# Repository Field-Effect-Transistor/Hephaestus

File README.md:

***

# Hephaestus: Smart Soldering Station (T12 + 858D)

**Бакалаврська кваліфікаційна робота**  
Розробка мікрокомп'ютерної системи керування двоканальною паяльною станцією з прецизійним терморегулюванням та апаратною відмовобезпекою.

## 📋 Основні можливості
*   **Два незалежні канали:** Контактний паяльник (жало T12) та компресорний термофен (858D).
*   **Прецизійна точність:** ПІД-регулювання з використанням зовнішнього 16-бітного АЦП та підсилювачів Zero-Drift.
*   **Апаратна безпека:** Електромеханічне реле із системою "самопідхвату" для захисту від термічного пробою.
*   **Багатозадачність (RTOS):** Використання FreeRTOS із витискальною багатозадачністю для суворого дотримання таймінгів алгоритму часового розділення (Time-Division).
*   **HIL Simulation:** Архітектура коду (Dependency Inversion) дозволяє компілювати та тестувати бізнес-логіку станції як нативну Linux/PC програму (Симулятор).
*   **Інтерфейс:** 1.3" OLED дисплей (u8g2) та апаратне декодування квадратурних енкодерів.

## 🛠 Технічний стек

### Апаратна частина (Hardware)
*   **MCU:** STM32F103C8T6 (ARM Cortex-M3)
*   **ADC:** ADS1115 (16-bit, I2C, ΔΣ)
*   **OpAmp:** OPA2333 / MCP6002
*   **Power:** Багаторівнева система живлення (24V, 5V, 3.3V Digital, 3.3V Analog)
*   **Drivers:** MOSFET (T12 / Турбіна), Triac BTA16 + Optocoupler (Нагрівач 220В)
*   **EDA:** KiCad 8.0

### Програмна частина (Firmware)
*   **Language:** C++17 / C
*   **Framework:** STM32 HAL / LL
*   **OS:** FreeRTOS (ARM CM3 Port / POSIX Port для симулятора)
*   **Build System:** CMake + Ninja
*   **IDE:** Visual Studio Code (C/C++ Extension Pack)

## 📂 Структура репозиторію

```text
├── firmware/
│   ├── App/             # Бізнес-логіка, Інтерфейси (C++)
│   │   ├── interfaces/  # Апаратні абстракції (Hardware Agnostic)
│   │   ├── logic/       # ПІД-регулятор, автомати станів кнопок
│   │   ├── platform/    # Реалізація інтерфейсів (STM32 HAL або PC Mocks)
│   │   └── ui/          # Керування дисплеєм (u8g2)
│   ├── Core/            # Згенерований CubeMX код (main.c, freertos.c)
│   ├── Drivers/         # STM32 HAL & CMSIS
│   └── Libs/            # Сторонні бібліотеки (u8g2, FreeRTOS POSIX)
│
├── hardware/            # Схемотехніка та плати (KiCad)
└── docs/                # Пояснювальна записка та даташити
```

## 🚀 Як зібрати проєкт

Проєкт підтримує дві цілі збірки: **Прошивка для мікроконтролера (STM32)** та **Симулятор для комп'ютера (Linux/PC)**.

### 1. Збірка Симулятора (Linux)
Симулятор компілює всю бізнес-логіку, запускає FreeRTOS поверх Pthreads операційної системи Linux та імітує датчики за допомогою об'єктів-заглушок (Mocks). Це дозволяє тестувати систему без реальної плати.

**Вимоги:** `cmake`, `ninja`, `gcc`, `g++`.

```bash
cd firmware
mkdir -p build_pc
rm -rf build_pc/* 

# Генеруємо конфігурацію для симулятора
cmake -DBUILD_SIMULATOR=ON -DCMAKE_C_COMPILER=gcc -DCMAKE_CXX_COMPILER=g++ . -G Ninja -B build_pc   

# Збираємо проєкт
ninja -C build_pc 

# Запускаємо симулятор
./build_pc/Hephaestus_Sim
```

### 2. Збірка Прошивки (STM32)
Для крос-компіляції під мікроконтролер використовується офіційний Toolchain.

**Вимоги:** `arm-none-eabi-gcc`, `cmake`, `ninja`.

```bash
cd firmware
mkdir -p build
rm -rf build/*

# Генеруємо конфігурацію для крос-компіляції
cmake -DCMAKE_TOOLCHAIN_FILE=cmake/gcc-arm-none-eabi.cmake . -G Ninja -B build

# Збираємо прошивку (.elf, .bin, .hex)
ninja -C build
```

***

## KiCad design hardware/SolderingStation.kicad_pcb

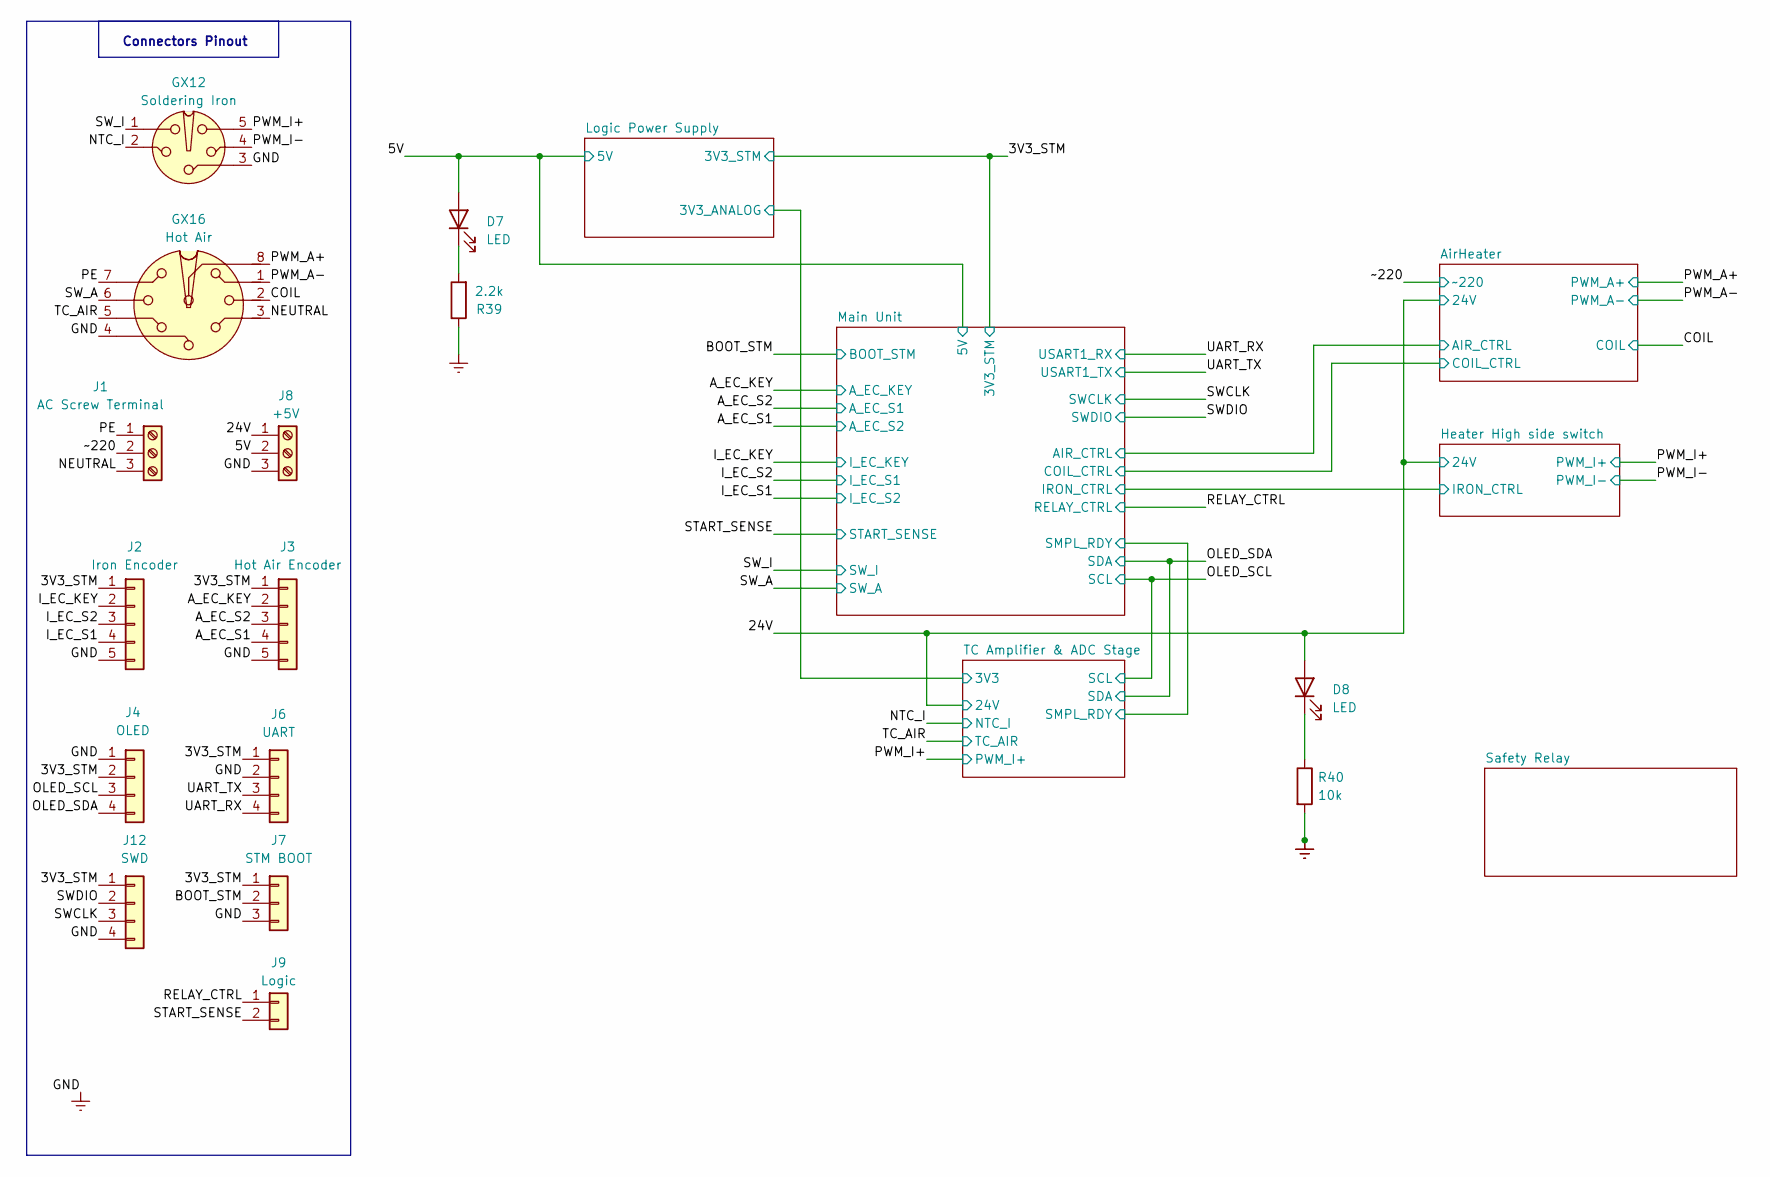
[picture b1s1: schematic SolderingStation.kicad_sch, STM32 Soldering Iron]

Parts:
D7, D8: LED; LED_0805_2012Metric_Pad1.15x1.40mm_HandSolder; LCSC C2286
GX12: Soldering Iron; GX-12-5
GX16: Hot Air; GX-16-8
J1: AC Screw Terminal; TerminalBlock_MaiXu_MX126-5.0-03P_1x03_P5.00mm
J2: Iron Encoder; PinHeader_1x05_P2.54mm_Vertical
J3: Hot Air Encoder; PinHeader_1x05_P2.54mm_Vertical
J4: OLED; PinHeader_1x04_P2.54mm_Vertical
J6: UART; PinHeader_1x04_P2.54mm_Vertical
J7: STM BOOT; PinHeader_1x03_P2.54mm_Vertical
J8: +5V; TerminalBlock_MaiXu_MX126-5.0-03P_1x03_P5.00mm
J9: Logic; PinHeader_1x02_P2.54mm_Vertical
J12: SWD; PinHeader_1x04_P2.54mm_Vertical
R39: 2.2k; R_0805_2012Metric_Pad1.20x1.40mm_HandSolder; LCSC C4190
R40: 10k; R_0805_2012Metric_Pad1.20x1.40mm_HandSolder; LCSC C25804

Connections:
/3V3_STM: J2.1, J3.1, J4.2, J6.1, J7.1, J12.1; also elsewhere on the board
/5V: D7.2 (A), J8.2; also elsewhere on the board
/24V: D8.2 (A), GX16.8, J8.1; also elsewhere on the board
/A_EC_KEY: J3.2; also elsewhere on the board
/A_EC_S1: J3.4; also elsewhere on the board
/A_EC_S2: J3.3; also elsewhere on the board
/BOOT_STM: J7.2; also elsewhere on the board
/COIL: GX16.2; also elsewhere on the board
/I_EC_KEY: J2.2; also elsewhere on the board
/I_EC_S1: J2.4; also elsewhere on the board
/I_EC_S2: J2.3; also elsewhere on the board
/NEUTRAL: GX16.3, J1.3
/NTC_I: GX12.2; also elsewhere on the board
/OLED_SCL: J4.3; also elsewhere on the board
/OLED_SDA: J4.4; also elsewhere on the board
/PE: GX16.7, J1.1
/PWM_A-: GX16.1; also elsewhere on the board
/PWM_I+: GX12.5; also elsewhere on the board
/RELAY_CTRL: J9.1; also elsewhere on the board
/START_SENSE: J9.2; also elsewhere on the board
/SWCLK: J12.3; also elsewhere on the board
/SWDIO: J12.2; also elsewhere on the board
/SW_A: GX16.6; also elsewhere on the board
/SW_I: GX12.1; also elsewhere on the board
/TC_AIR: GX16.5; also elsewhere on the board
/UART_RX: J6.4; also elsewhere on the board
/UART_TX: J6.3; also elsewhere on the board
/~220: J1.2; also elsewhere on the board
GNDREF: GX12.3, GX12.4, GX16.4, J2.5, J3.5, J4.1, J6.2, J7.3, J8.3, J12.4, R39.1, R40.2; also elsewhere on the board
unnamed: D7.1 (K), R39.2
unnamed: D8.1 (K), R40.1

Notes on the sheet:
Connectors Pinout

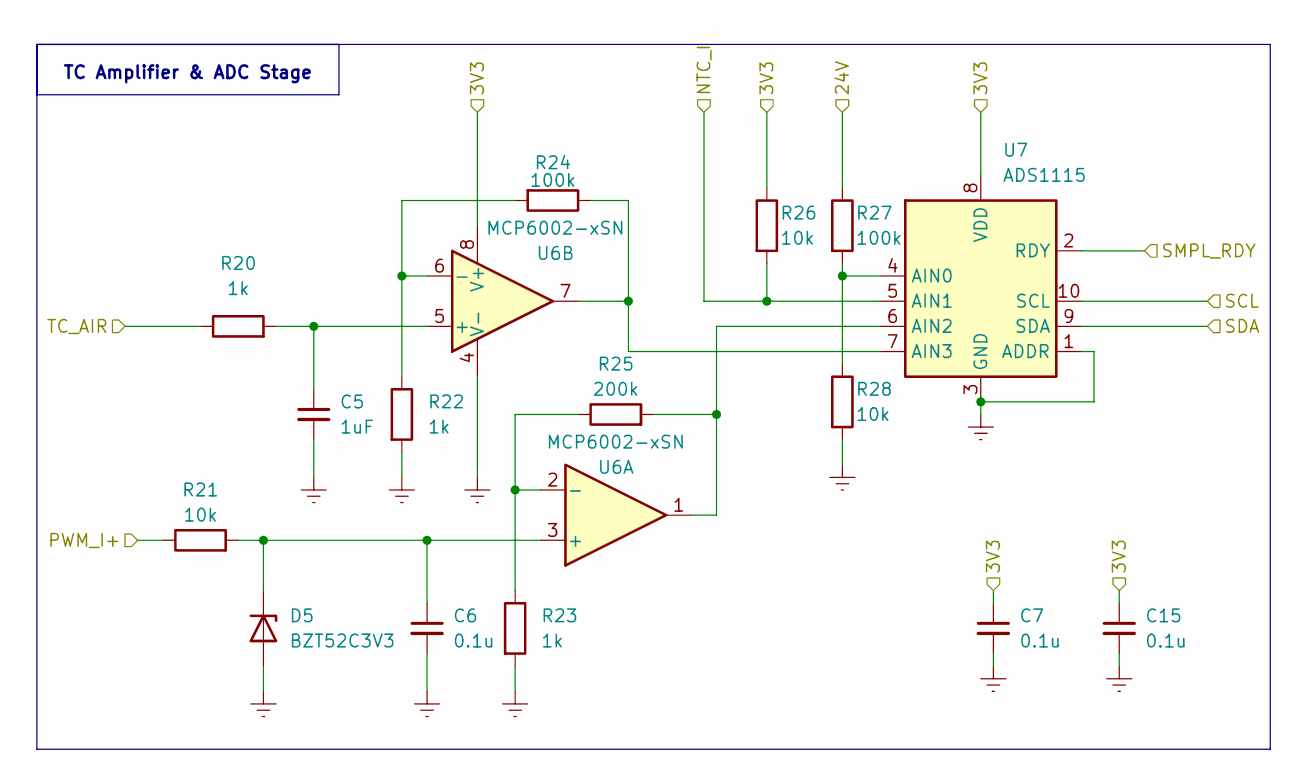
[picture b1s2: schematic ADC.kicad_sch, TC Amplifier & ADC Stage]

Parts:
C5: 1uF; C_0805_2012Metric_Pad1.18x1.45mm_HandSolder; LCSC C1634
C6, C7, C15: 0.1u; C_0805_2012Metric_Pad1.18x1.45mm_HandSolder; LCSC C14663
D5: BZT52C3V3; D_DO-35_SOD27_P2.54mm_Vertical_AnodeUp
R20, R22, R23: 1k; R_0805_2012Metric_Pad1.20x1.40mm_HandSolder; LCSC C21190
R21, R26, R28: 10k; R_0805_2012Metric_Pad1.20x1.40mm_HandSolder; LCSC C25804
R24, R27: 100k; R_0805_2012Metric_Pad1.20x1.40mm_HandSolder; LCSC C25803
R25: 200k; R_0805_2012Metric_Pad1.20x1.40mm_HandSolder; LCSC C25811
U6: MCP6002-xSN; SOIC-8_3.9x4.9mm_P1.27mm
U7: ADS1115; MSOP-10_3x3mm_P0.5mm

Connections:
/24V: R27.1; also elsewhere on the board
/Logic Power Supply/3V3_ANALOG: C7.1, C15.1, R26.1, U6.8 (V+), U7.8 (VDD); also elsewhere on the board
/Main Unit/SMPL_RDY: U7.2 (RDY); also elsewhere on the board
/NTC_I: R26.2, U7.5 (AIN1); also elsewhere on the board
/OLED_SCL: U7.10 (SCL); also elsewhere on the board
/OLED_SDA: U7.9 (SDA); also elsewhere on the board
/PWM_I+: R21.1; also elsewhere on the board
/TC_AIR: R20.1; also elsewhere on the board
GNDREF: C5.2, C6.2, C7.2, C15.2, D5.2 (A), R22.2, R23.2, R28.2, U6.4 (V-), U7.1 (ADDR), U7.3 (GND); also elsewhere on the board
unnamed: C6.1, D5.1 (K), R21.2, U6.3 (+)
unnamed: R23.1, R25.1, U6.2 (-)
unnamed: C5.1, R20.2, U6.5 (+)
unnamed: R22.1, R24.2, U6.6 (-)
unnamed: R27.2, R28.1, U7.4 (AIN0)
unnamed: R25.2, U6.1, U7.6 (AIN2)
unnamed: R24.1, U6.7, U7.7 (AIN3)

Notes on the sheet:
TC Amplifier & ADC Stage

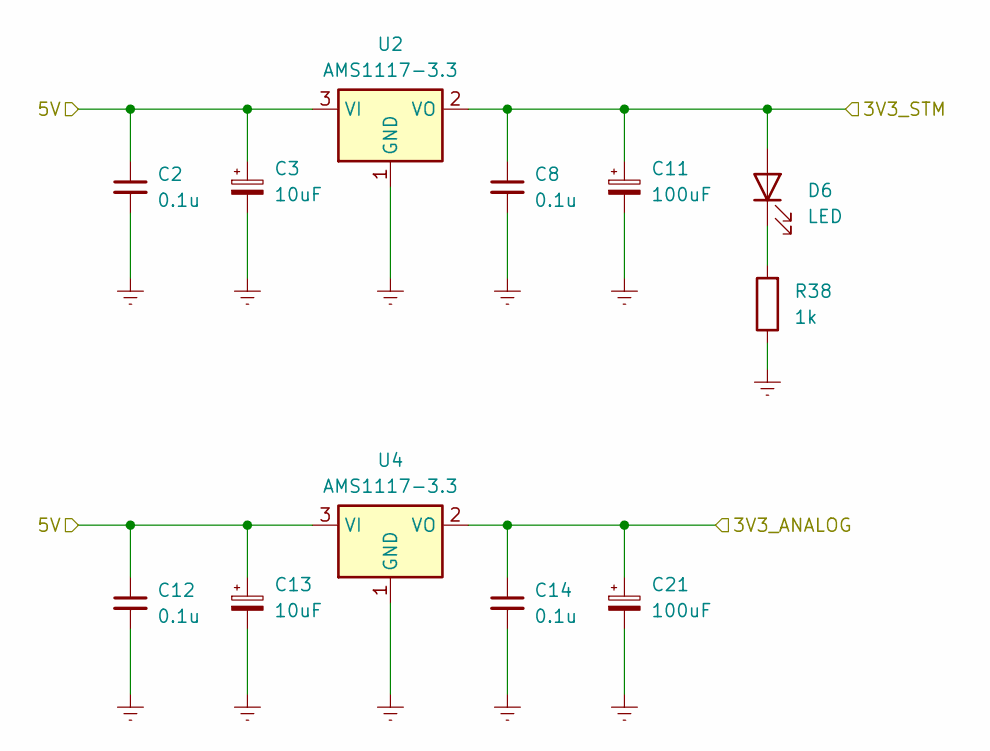
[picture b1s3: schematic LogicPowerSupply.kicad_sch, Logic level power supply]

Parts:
C2, C8, C12, C14: 0.1u; C_0805_2012Metric_Pad1.18x1.45mm_HandSolder; LCSC C14663
C3, C13: 10uF; CP_Radial_D5.0mm_P2.00mm
C11, C21: 100uF; CP_Radial_D6.3mm_P2.50mm
D6: LED; LED_0805_2012Metric_Pad1.15x1.40mm_HandSolder; LCSC C2286
R38: 1k; R_0805_2012Metric_Pad1.20x1.40mm_HandSolder; LCSC C21190
U2, U4: AMS1117-3.3; SOT-223-3_TabPin2; LCSC C6186

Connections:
/3V3_STM: C8.1, C11.1, D6.2 (A), U2.2 (VO); also elsewhere on the board
/5V: C2.1, C3.1, C12.1, C13.1, U2.3 (VI), U4.3 (VI); also elsewhere on the board
/Logic Power Supply/3V3_ANALOG: C14.1, C21.1, U4.2 (VO); also elsewhere on the board
GNDREF: C2.2, C3.2, C8.2, C11.2, C12.2, C13.2, C14.2, C21.2, R38.1, U2.1 (GND), U4.1 (GND); also elsewhere on the board
unnamed: D6.1 (K), R38.2

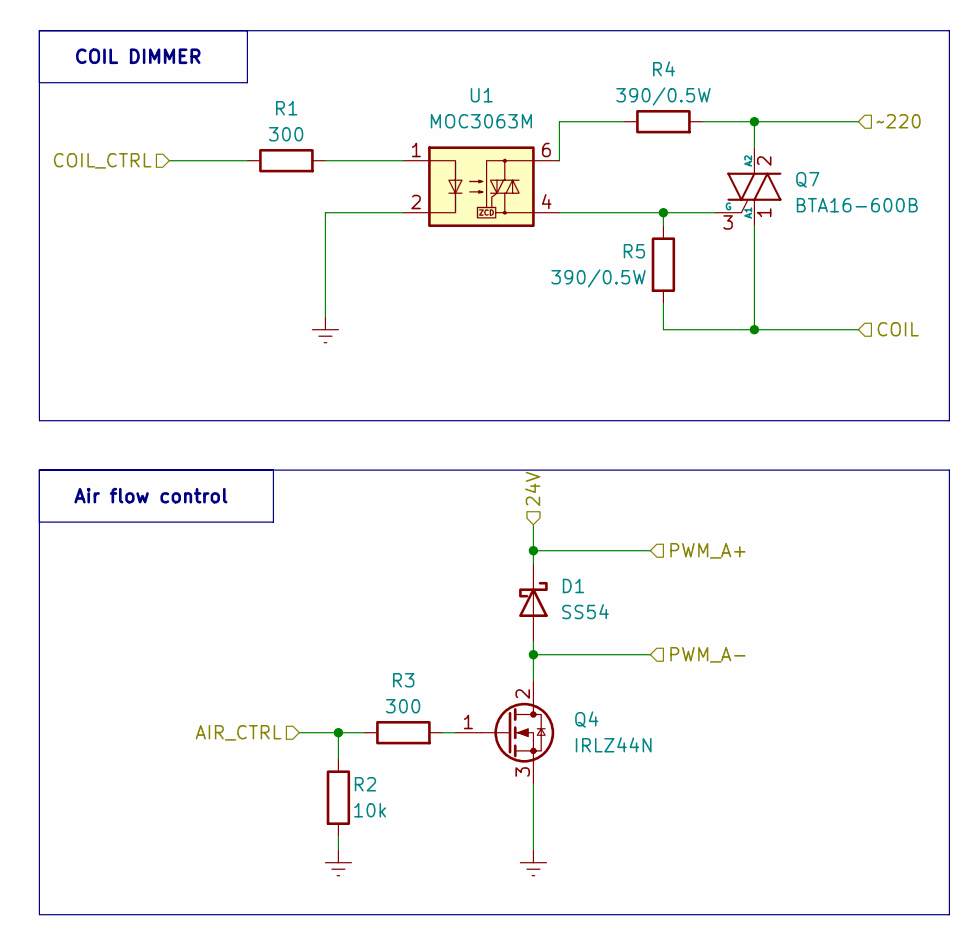
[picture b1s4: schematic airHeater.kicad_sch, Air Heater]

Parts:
D1: SS54; D_SMA; LCSC C22452
Q4: IRLZ44N; TO-220-3_Vertical
Q7: BTA16-600B; TO-220-3_Vertical
R1, R3: 300; R_0805_2012Metric_Pad1.20x1.40mm_HandSolder; LCSC C23025
R2: 10k; R_0805_2012Metric_Pad1.20x1.40mm_HandSolder; LCSC C25804
R4, R5: 390/0.5W; R_Axial_DIN0309_L9.0mm_D3.2mm_P12.70mm_Horizontal
U1: MOC3063M; DIP-6_W7.62mm_LongPads

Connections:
/24V: D1.1 (K); also elsewhere on the board
/AirHeater/AIR_CTRL: R2.1, R3.1; also elsewhere on the board
/AirHeater/COIL_CTRL: R1.1; also elsewhere on the board
/COIL: Q7.1 (A1), R5.2; also elsewhere on the board
/PWM_A-: D1.2 (A), Q4.2 (D); also elsewhere on the board
/~220: Q7.2 (A2), R4.2; also elsewhere on the board
GNDREF: Q4.3 (S), R2.2, U1.2; also elsewhere on the board
unnamed: Q4.1 (G), R3.2
unnamed: Q7.3 (G), R5.1, U1.4
unnamed: R1.2, U1.1
unnamed: R4.1, U1.6

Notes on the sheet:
COIL DIMMER
Air flow control

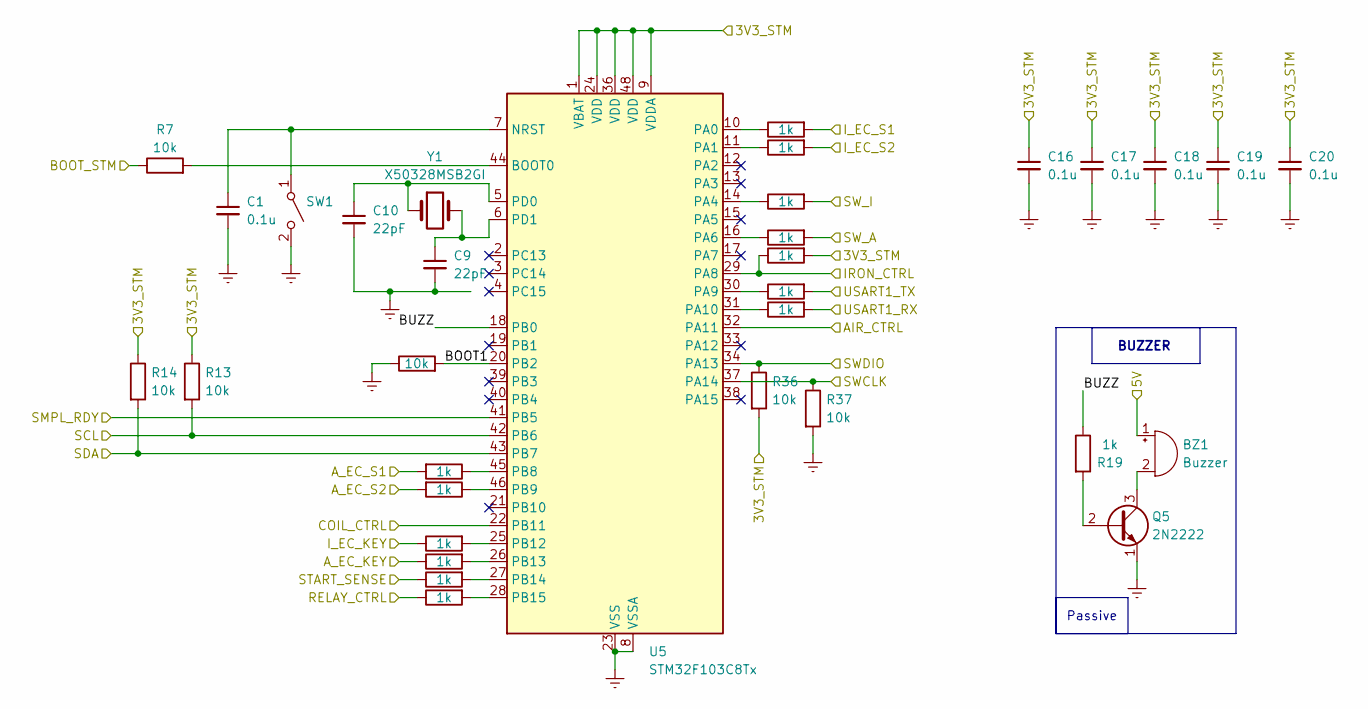
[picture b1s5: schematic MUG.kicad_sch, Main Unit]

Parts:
BZ1: Buzzer; Buzzer_12x9.5RM7.6
C1, C16, C17, C18, C19, C20: 0.1u; C_0805_2012Metric_Pad1.18x1.45mm_HandSolder; LCSC C14663
C9, C10: 22pF; C_0805_2012Metric_Pad1.18x1.45mm_HandSolder; LCSC C1653
Q5: 2N2222; TO-92_Inline; LCSC C2146
R6, R7, R13, R14, R36, R37: 10k; R_0805_2012Metric_Pad1.20x1.40mm_HandSolder; LCSC C25804
R12, R15, R17, R18, R19, R29, R30, R31, R32, R33, R34, R35, R41, R42: 1k; R_0805_2012Metric_Pad1.20x1.40mm_HandSolder; LCSC C21190
SW1: SW_SPST; SW_PUSH_6mm_H8mm
U5: STM32F103C8Tx; LQFP-48_7x7mm_P0.5mm
Y1: X50328MSB2GI; Crystal_SMD_5032-2Pin_5.0x3.2mm; LCSC C115962

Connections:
/3V3_STM: C16.1, C17.1, C18.1, C19.1, C20.1, R13.1, R14.1, R15.2, R36.2, U5.1 (VBAT), U5.9 (VDDA), U5.24 (VDD), U5.36 (VDD), U5.48 (VDD); also elsewhere on the board
/5V: BZ1.1 (+); also elsewhere on the board
/A_EC_KEY: R30.1; also elsewhere on the board
/A_EC_S1: R32.2; also elsewhere on the board
/A_EC_S2: R31.2; also elsewhere on the board
/AirHeater/AIR_CTRL: U5.32 (PA11); also elsewhere on the board
/AirHeater/COIL_CTRL: U5.22 (PB11); also elsewhere on the board
/BOOT_STM: R7.1; also elsewhere on the board
/Heater High side switch/IRON_CTRL: R15.1, U5.29 (PA8); also elsewhere on the board
/I_EC_KEY: R29.1; also elsewhere on the board
/I_EC_S1: R18.2; also elsewhere on the board
/I_EC_S2: R17.2; also elsewhere on the board
/Main Unit/BOOT1: R6.2, U5.20 (PB2)
/Main Unit/BUZZ: R19.1, U5.18 (PB0)
/Main Unit/SMPL_RDY: U5.41 (PB5); also elsewhere on the board
/OLED_SCL: R13.2, U5.42 (PB6); also elsewhere on the board
/OLED_SDA: R14.2, U5.43 (PB7); also elsewhere on the board
/RELAY_CTRL: R33.1; also elsewhere on the board
/START_SENSE: R12.1; also elsewhere on the board
/SWCLK: R37.1, U5.37 (PA14); also elsewhere on the board
/SWDIO: R36.1, U5.34 (PA13); also elsewhere on the board
/SW_A: R34.2; also elsewhere on the board
/SW_I: R35.2; also elsewhere on the board
/UART_RX: R42.2; also elsewhere on the board
/UART_TX: R41.2; also elsewhere on the board
GNDREF: C1.2, C9.2, C10.2, C16.2, C17.2, C18.2, C19.2, C20.2, Q5.1 (E), R6.1, R37.2, SW1.2 (B), U5.8 (VSSA), U5.23 (VSS), U5.35 (VSS), U5.47 (VSS); also elsewhere on the board
unnamed: BZ1.2 (-), Q5.3 (C)
unnamed: Q5.2 (B), R19.2
unnamed: C1.1, SW1.1 (A), U5.7 (NRST)
unnamed: R7.2, U5.44 (BOOT0)
unnamed: R17.1, U5.10 (PA0)
unnamed: R18.1, U5.11 (PA1)
unnamed: R35.1, U5.14 (PA4)
unnamed: R34.1, U5.16 (PA6)
unnamed: R41.1, U5.30 (PA9)
unnamed: R42.1, U5.31 (PA10)
unnamed: R31.1, U5.45 (PB8)
unnamed: R32.1, U5.46 (PB9)
unnamed: R29.2, U5.25 (PB12)
unnamed: R30.2, U5.26 (PB13)
unnamed: R12.2, U5.27 (PB14)
unnamed: R33.2, U5.28 (PB15)
unnamed: C10.1, U5.5 (PD0), Y1.1
unnamed: C9.1, U5.6 (PD1), Y1.2

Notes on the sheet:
Passive
BUZZER

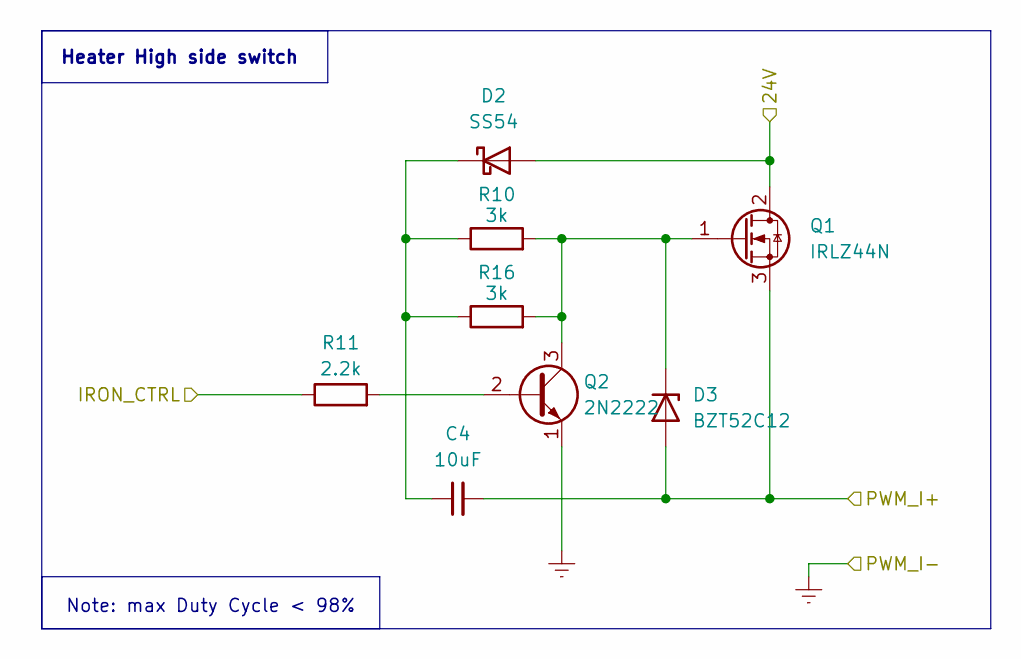
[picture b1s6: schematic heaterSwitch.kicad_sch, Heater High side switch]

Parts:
C4: 10uF; C_1206_3216Metric; LCSC C13585
D2: SS54; D_SMA; LCSC C22452
D3: BZT52C12; D_DO-35_SOD27_P2.54mm_Vertical_AnodeUp
Q1: IRLZ44N; TO-220-3_Vertical
Q2: 2N2222; TO-92_Inline; LCSC C2146
R10, R16: 3k; R_Axial_DIN0207_L6.3mm_D2.5mm_P7.62mm_Horizontal
R11: 2.2k; R_0805_2012Metric_Pad1.20x1.40mm_HandSolder; LCSC C4190

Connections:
/24V: D2.2 (A), Q1.2 (D); also elsewhere on the board
/Heater High side switch/IRON_CTRL: R11.1; also elsewhere on the board
/PWM_I+: C4.2, D3.2 (A), Q1.3 (S); also elsewhere on the board
GNDREF: Q2.1 (E); also elsewhere on the board
unnamed: C4.1, D2.1 (K), R10.1, R16.1
unnamed: D3.1 (K), Q1.1 (G), Q2.3 (C), R10.2, R16.2
unnamed: Q2.2 (B), R11.2

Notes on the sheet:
Note: max Duty Cycle < 98%
Heater High side switch

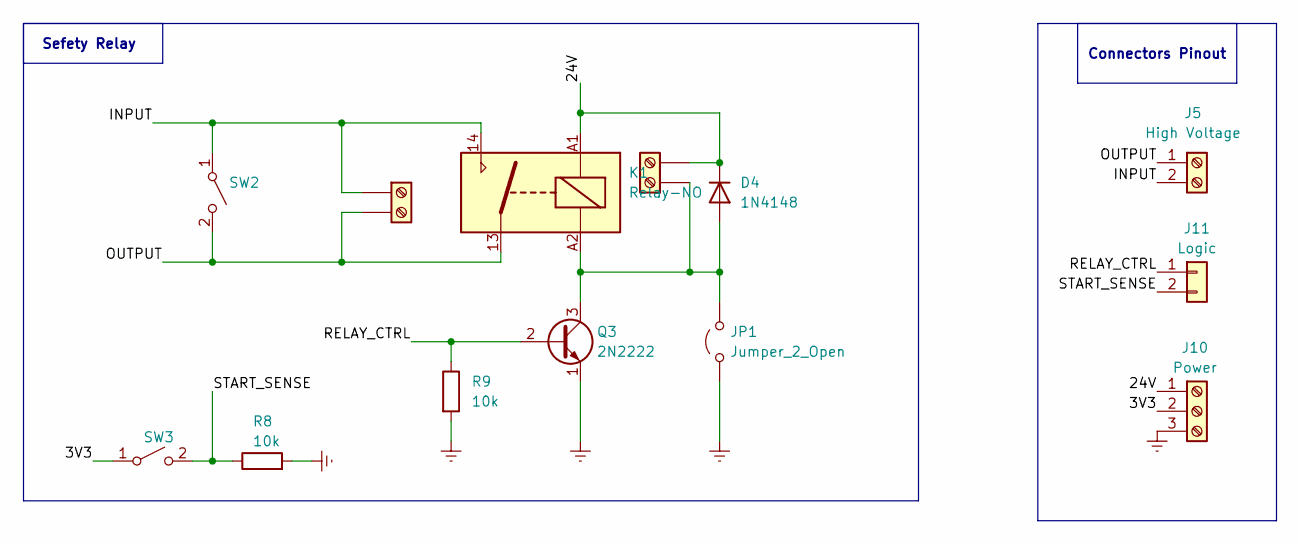
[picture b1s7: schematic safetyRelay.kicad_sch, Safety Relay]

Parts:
D4: 1N4148; D_SOD-123F; LCSC C2128
J5: High Voltage; TerminalBlock_MaiXu_MX126-5.0-02P_1x02_P5.00mm
J10: Power; TerminalBlock_MaiXu_MX126-5.0-03P_1x03_P5.00mm
J11: Logic; PinHeader_1x02_P2.54mm_Vertical
J13: Relay Contact; TerminalBlock_MaiXu_MX126-5.0-02P_1x02_P5.00mm
J14: Relay Coil; TerminalBlock_MaiXu_MX126-5.0-02P_1x02_P5.00mm
JP1: Jumper_2_Open; PinHeader_1x03_P2.54mm_Vertical
K1: Relay-NO; TerminalBlock_MaiXu_MX126-5.0-04P_1x04_P5.00mm
Q3: 2N2222; TO-92_Inline; LCSC C2146
R8, R9: 10k; R_0805_2012Metric_Pad1.20x1.40mm_HandSolder; LCSC C25804
SW2: SW_SPST; TerminalBlock_MaiXu_MX126-5.0-02P_1x02_P5.00mm
SW3: SW_SPST; PinHeader_1x02_P2.54mm_Vertical

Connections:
/Safety Relay/3V3: J10.2, SW3.1 (A)
/Safety Relay/24V: D4.1 (K), J10.1, J14.2, K1.A1
/Safety Relay/INPUT: J5.2, J13.1, K1.14, SW2.1 (A)
/Safety Relay/OUTPUT: J5.1, J13.2, K1.13, SW2.2 (B)
/Safety Relay/RELAY_CTRL: J11.1, Q3.2 (B), R9.1
/Safety Relay/START_SENSE: J11.2, R8.1, SW3.2 (B)
GNDREF: J10.3, JP1.1 (A), Q3.1 (E), R8.2, R9.2; also elsewhere on the board
unnamed: D4.2 (A), J14.1, JP1.2 (B), K1.A2, Q3.3 (C)

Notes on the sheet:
Sefety Relay
Connectors Pinout

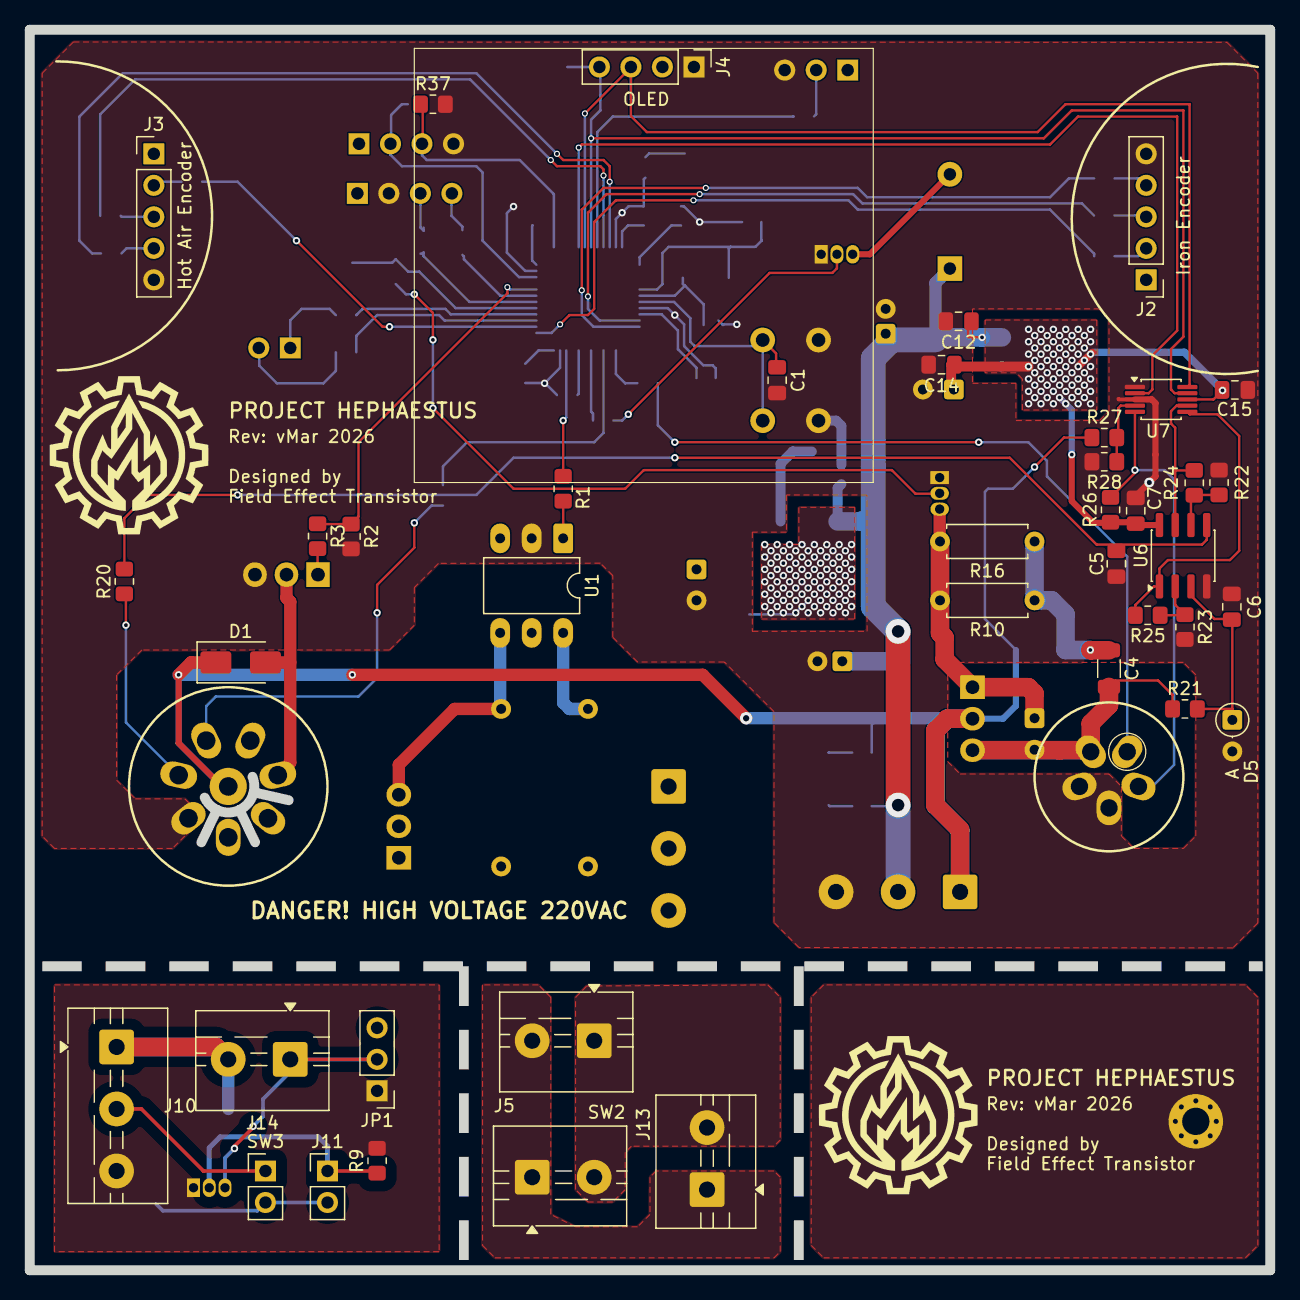
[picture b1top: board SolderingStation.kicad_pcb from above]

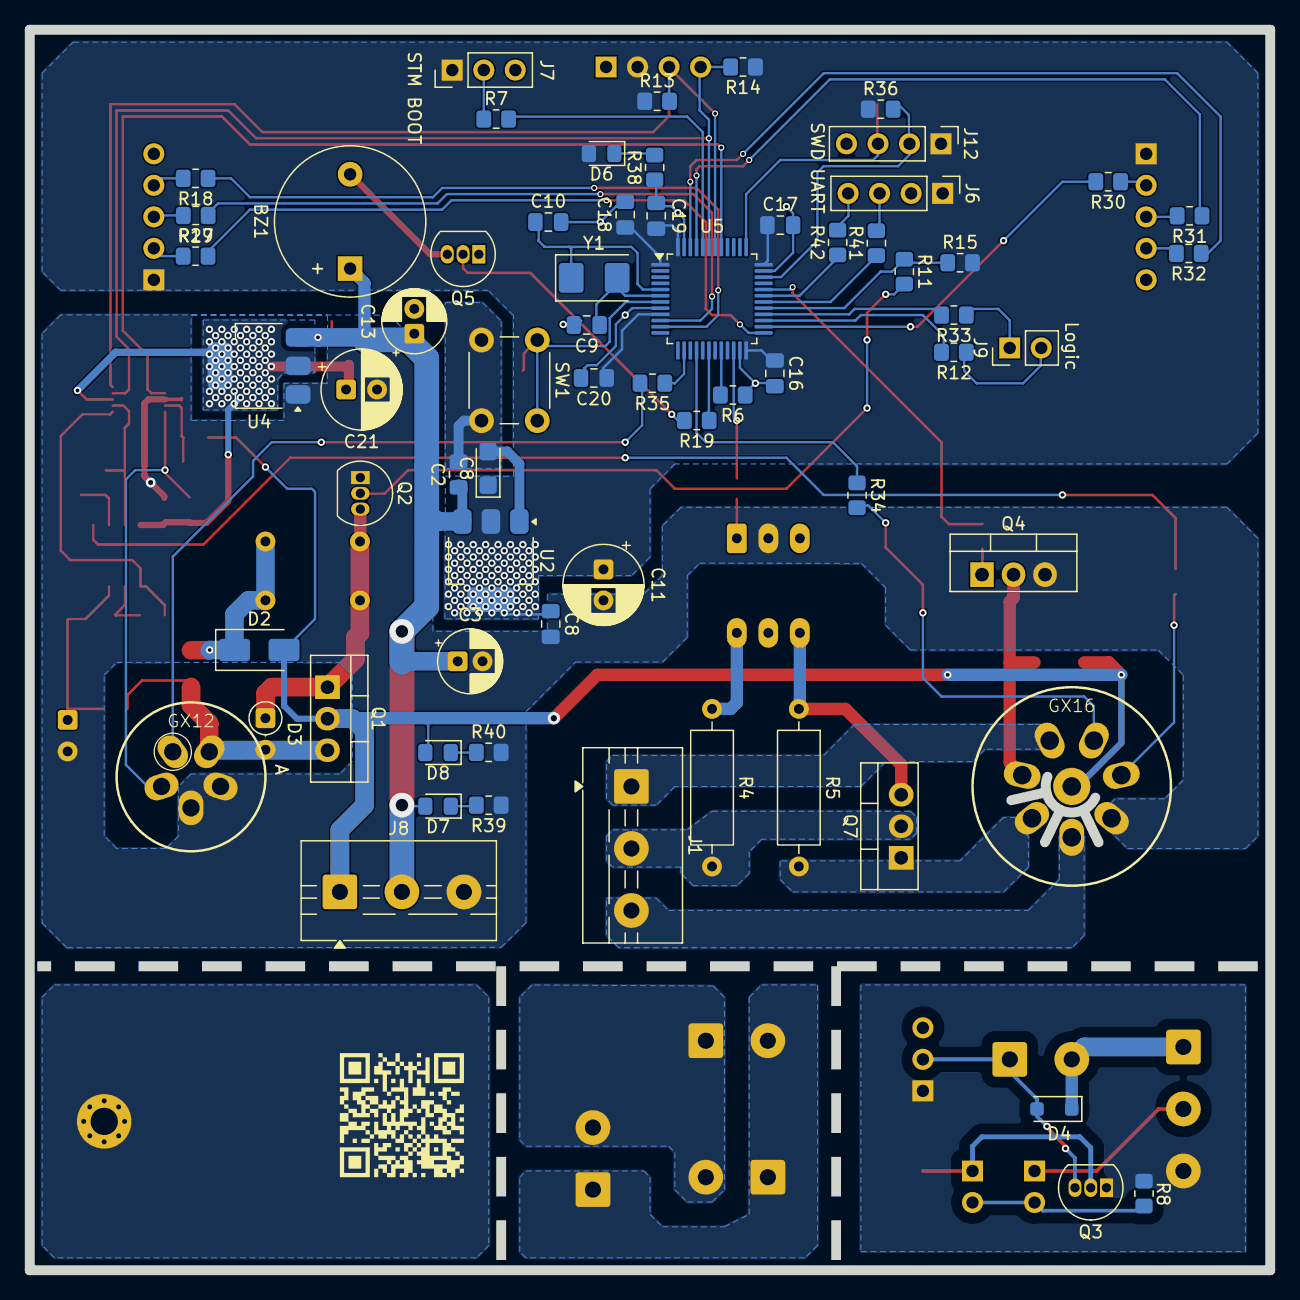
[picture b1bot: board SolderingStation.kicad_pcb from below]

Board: 2 copper layers, 100.0 x 100.0 mm, 106 parts (66 on the bottom side), 78 nets.

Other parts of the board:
C8#2: 0.1u; C_0805_2012Metric_Pad1.18x1.45mm_HandSolder

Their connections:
/3V3_STM: C8#2.1; also elsewhere on the board
GNDREF: C8#2.2; also elsewhere on the board

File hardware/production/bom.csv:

Designator,Footprint,Quantity,Value,LCSC Part #
BZ1,Buzzer_12x9.5RM7.6,1,Buzzer,
"C1, C12, C14, C15, C16, C17, C18, C19, C2, C20, C6, C7, C8",0805,13,0.1u,C14663
"C10, C9",0805,2,22pF,C1653 
"C11, C21",CP_Radial_D6.3mm_P2.50mm,2,100uF,
"C13, C3",CP_Radial_D5.0mm_P2.00mm,2,10uF,
C4,1206,1,10uF,C13585
C5,0805,1,1uF,C1634
C8_2,CP_EIA-3216-18_Kemet-A,1,22uF,
"D1, D2",D_SMA,2,SS54,C22452
D3,D_DO-35_SOD27_P2.54mm_Vertical_AnodeUp,1,BZT52C12,
D4,D_SOD-123F,1,1N4148,C2128
D5,D_DO-35_SOD27_P2.54mm_Vertical_AnodeUp,1,BZT52C3V3,
"D6, D7, D8",0805,3,LED,C2286
GX12,GX-12-5,1,Soldering Iron,
GX16,GX-16-8,1,Hot Air,
J1,TerminalBlock_MaiXu_MX126-5.0-03P_1x03_P5.00mm,1,AC Screw Terminal,
J10,TerminalBlock_MaiXu_MX126-5.0-03P_1x03_P5.00mm,1,Power,
"J11, J9",PinHeader_1x02_P2.54mm_Vertical,2,Logic,
J12,PinHeader_1x04_P2.54mm_Vertical,1,SWD,
J13,TerminalBlock_MaiXu_MX126-5.0-02P_1x02_P5.00mm,1,Relay Contact,
J14,TerminalBlock_MaiXu_MX126-5.0-02P_1x02_P5.00mm,1,Relay Coil,
J2,PinHeader_1x05_P2.54mm_Vertical,1,Iron Encoder,
J3,PinHeader_1x05_P2.54mm_Vertical,1,Hot Air Encoder,
J4,PinHeader_1x04_P2.54mm_Vertical,1,OLED,
J5,TerminalBlock_MaiXu_MX126-5.0-02P_1x02_P5.00mm,1,High Voltage,
J6,PinHeader_1x04_P2.54mm_Vertical,1,UART,
J7,PinHeader_1x03_P2.54mm_Vertical,1,STM BOOT,
J8,TerminalBlock_MaiXu_MX126-5.0-03P_1x03_P5.00mm,1,+5V,
JP1,PinHeader_1x03_P2.54mm_Vertical,1,Jumper_2_Open,
"Q1, Q4",TO-220-3_Vertical,2,IRLZ44N,
"Q2, Q3, Q5",TO-92_Inline,3,2N2222,C2146
Q7,TO-220-3_Vertical,1,BTA16-600B,
"R1, R3",0805,2,300,C23025
"R10, R16",R_Axial_DIN0207_L6.3mm_D2.5mm_P7.62mm_Horizontal,2,3k,
"R11, R39",0805,2,2.2k,C4190
"R12, R15, R17, R18, R19, R20, R22, R23, R29, R30, R31, R32, R33, R34, R35, R38, R41, R42",0805,18,1k,C21190
"R13, R14, R2, R21, R26, R28, R36, R37, R40, R6, R7, R8, R9",0805,13,10k,C25804
"R24, R27",0805,2,100k,C25803
R25,0805,1,200k,C25811
"R4, R5",R_Axial_DIN0309_L9.0mm_D3.2mm_P12.70mm_Horizontal,2,390/0.5W,
SW1,SW_PUSH_6mm_H8mm,1,SW_SPST,
SW2,TerminalBlock_MaiXu_MX126-5.0-02P_1x02_P5.00mm,1,SW_SPST,
SW3,PinHeader_1x02_P2.54mm_Vertical,1,SW_SPST,
U1,DIP-6_W7.62mm_LongPads,1,MOC3063M,
"U2, U4",SOT-223-3_TabPin2,2,AMS1117-3.3,C6186 
U5,LQFP-48_7x7mm_P0.5mm,1,STM32F103C8Tx,
U6,SOIC-8_3.9x4.9mm_P1.27mm,1,MCP6002-xSN,
U7,MSOP-10_3x3mm_P0.5mm,1,ADS1115,
Y1,Crystal_SMD_5032-2Pin_5.0x3.2mm,1,X50328MSB2GI,C115962

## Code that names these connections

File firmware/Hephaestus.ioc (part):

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Mcu.Name=STM32F103C(8-B)Tx
Mcu.Package=LQFP48
Mcu.UserName=STM32F103C8Tx
PA0-WKUP.Signal=S_TIM2_CH1_ETR
PA1.Signal=S_TIM2_CH2
PA10.Mode=Asynchronous
PA10.Signal=USART1_RX
PA11.Signal=S_TIM1_CH4
PA13.Mode=Serial_Wire
PA13.Signal=SYS_JTMS-SWDIO
PA14.Mode=Serial_Wire
PA14.Signal=SYS_JTCK-SWCLK
PA4.GPIOParameters=GPIO_PuPd
PA4.GPIO_PuPd=GPIO_PULLUP
PA4.Signal=GPXTI4
PA6.GPIOParameters=GPIO_PuPd
PA6.GPIO_PuPd=GPIO_PULLUP
PA6.Signal=GPXTI6
PA8.Signal=S_TIM1_CH1
PA9.Mode=Asynchronous
PA9.Signal=USART1_TX
PB0.Signal=S_TIM3_CH3
PB11.Signal=GPIO_Output
PB12.GPIOParameters=GPIO_PuPd
PB12.GPIO_PuPd=GPIO_PULLUP
PB12.Signal=GPXTI12
PB13.GPIOParameters=GPIO_PuPd
PB13.GPIO_PuPd=GPIO_PULLUP
PB13.Signal=GPXTI13
PB14.GPIOParameters=GPIO_PuPd
PB14.GPIO_PuPd=GPIO_NOPULL
PB14.Signal=GPIO_Input
PB15.Signal=GPIO_Output
PB5.Signal=GPXTI5
PB6.Signal=S_TIM4_CH1
PB7.Signal=S_TIM4_CH2
PB8.Mode=I2C
PB8.Signal=I2C1_SCL
PB9.Mode=I2C
PB9.Signal=I2C1_SDA
PC13-TAMPER-RTC.Signal=GPIO_Output
PD0-OSC_IN.Mode=HSE-External-Oscillator
PD0-OSC_IN.Signal=RCC_OSC_IN
PD1-OSC_OUT.Mode=HSE-External-Oscillator
PD1-OSC_OUT.Signal=RCC_OSC_OUT
RCC.SYSCLKFreq_VALUE=72000000
RCC.SYSCLKSource=RCC_SYSCLKSOURCE_PLLCLK
board=custom

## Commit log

2026-01-13 init
2026-01-16 first steps
    Soldering Iron & Hot Air pinout added
    ADC logic added
2026-01-18 fix: ADC
    24V converting fix
    PWD_I resistor fix
2026-01-18 feature: heater switch
2026-01-19 feature: fan logic
2026-01-20 feature: basic nodes
2026-02-04 peripherals done
2026-02-11 feature: safety relay
2026-02-24 mvp
    features:
    Logic Power Supply
    Safety Relay
    Main Unit
2026-03-07 starting pcb
2026-03-09 fast commit
2026-03-15 pcb mvp
2026-04-04 last
2026-05-15 fast:
2026-05-15 stm32 init
2026-05-15 feat: exti_register
2026-05-15 feat: button
2026-05-19 feat(system): logger added
2026-05-19 feat(system): button
2026-05-19 refactor(uart_log_sink)
2026-05-19 feature(system): encoder
2026-05-20 feature(system): oled + basic logic
2026-05-26 fast
2026-05-28 refactor
2026-05-28 linux port
2026-05-28 feat: introduce Hardware Abstraction Layer and PC Simulator
    - Refactored architecture using Dependency Injection (IAdc, IEncoder, etc.)
    - Added PC Simulator with SDL2 for testing UI and logic on Linux
    - Decoupled u8g2 display manager from hardware I2C
    - Centralized StationManager to handle business logic
    - Introduced thread-safe SDL event loop for input simulation
2026-05-28 feat(logic): integrate PID controller into heater channel control loop
2026-05-28 feat(ui): implement interactive screens (Menu, PID, System Info) and routing
2026-05-29 feat(core): separate control loop to RTOS task and implement TDM for ADC
2026-05-29 feat: implement auto-sleep via stand sensors and hot air fan control
2026-05-29 feat(storage): implement persistent user settings loading and saving
2026-05-29 feat(core): add thermal runaway protection and deferred config saving
2026-05-29 feat(core): add 3-point temperature calibration and buzzer feedback
2026-05-29 fix(pc mock)
2026-05-29 refactor(hw): remap PWM pins and introduce software PWM for 220V heater
2026-05-29 feat(ui): add calibration screen skeleton to main menu
2026-05-29 feat(safety): implement hardware watchdog and critical fault power kill

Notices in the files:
README.md:
License: MIT
